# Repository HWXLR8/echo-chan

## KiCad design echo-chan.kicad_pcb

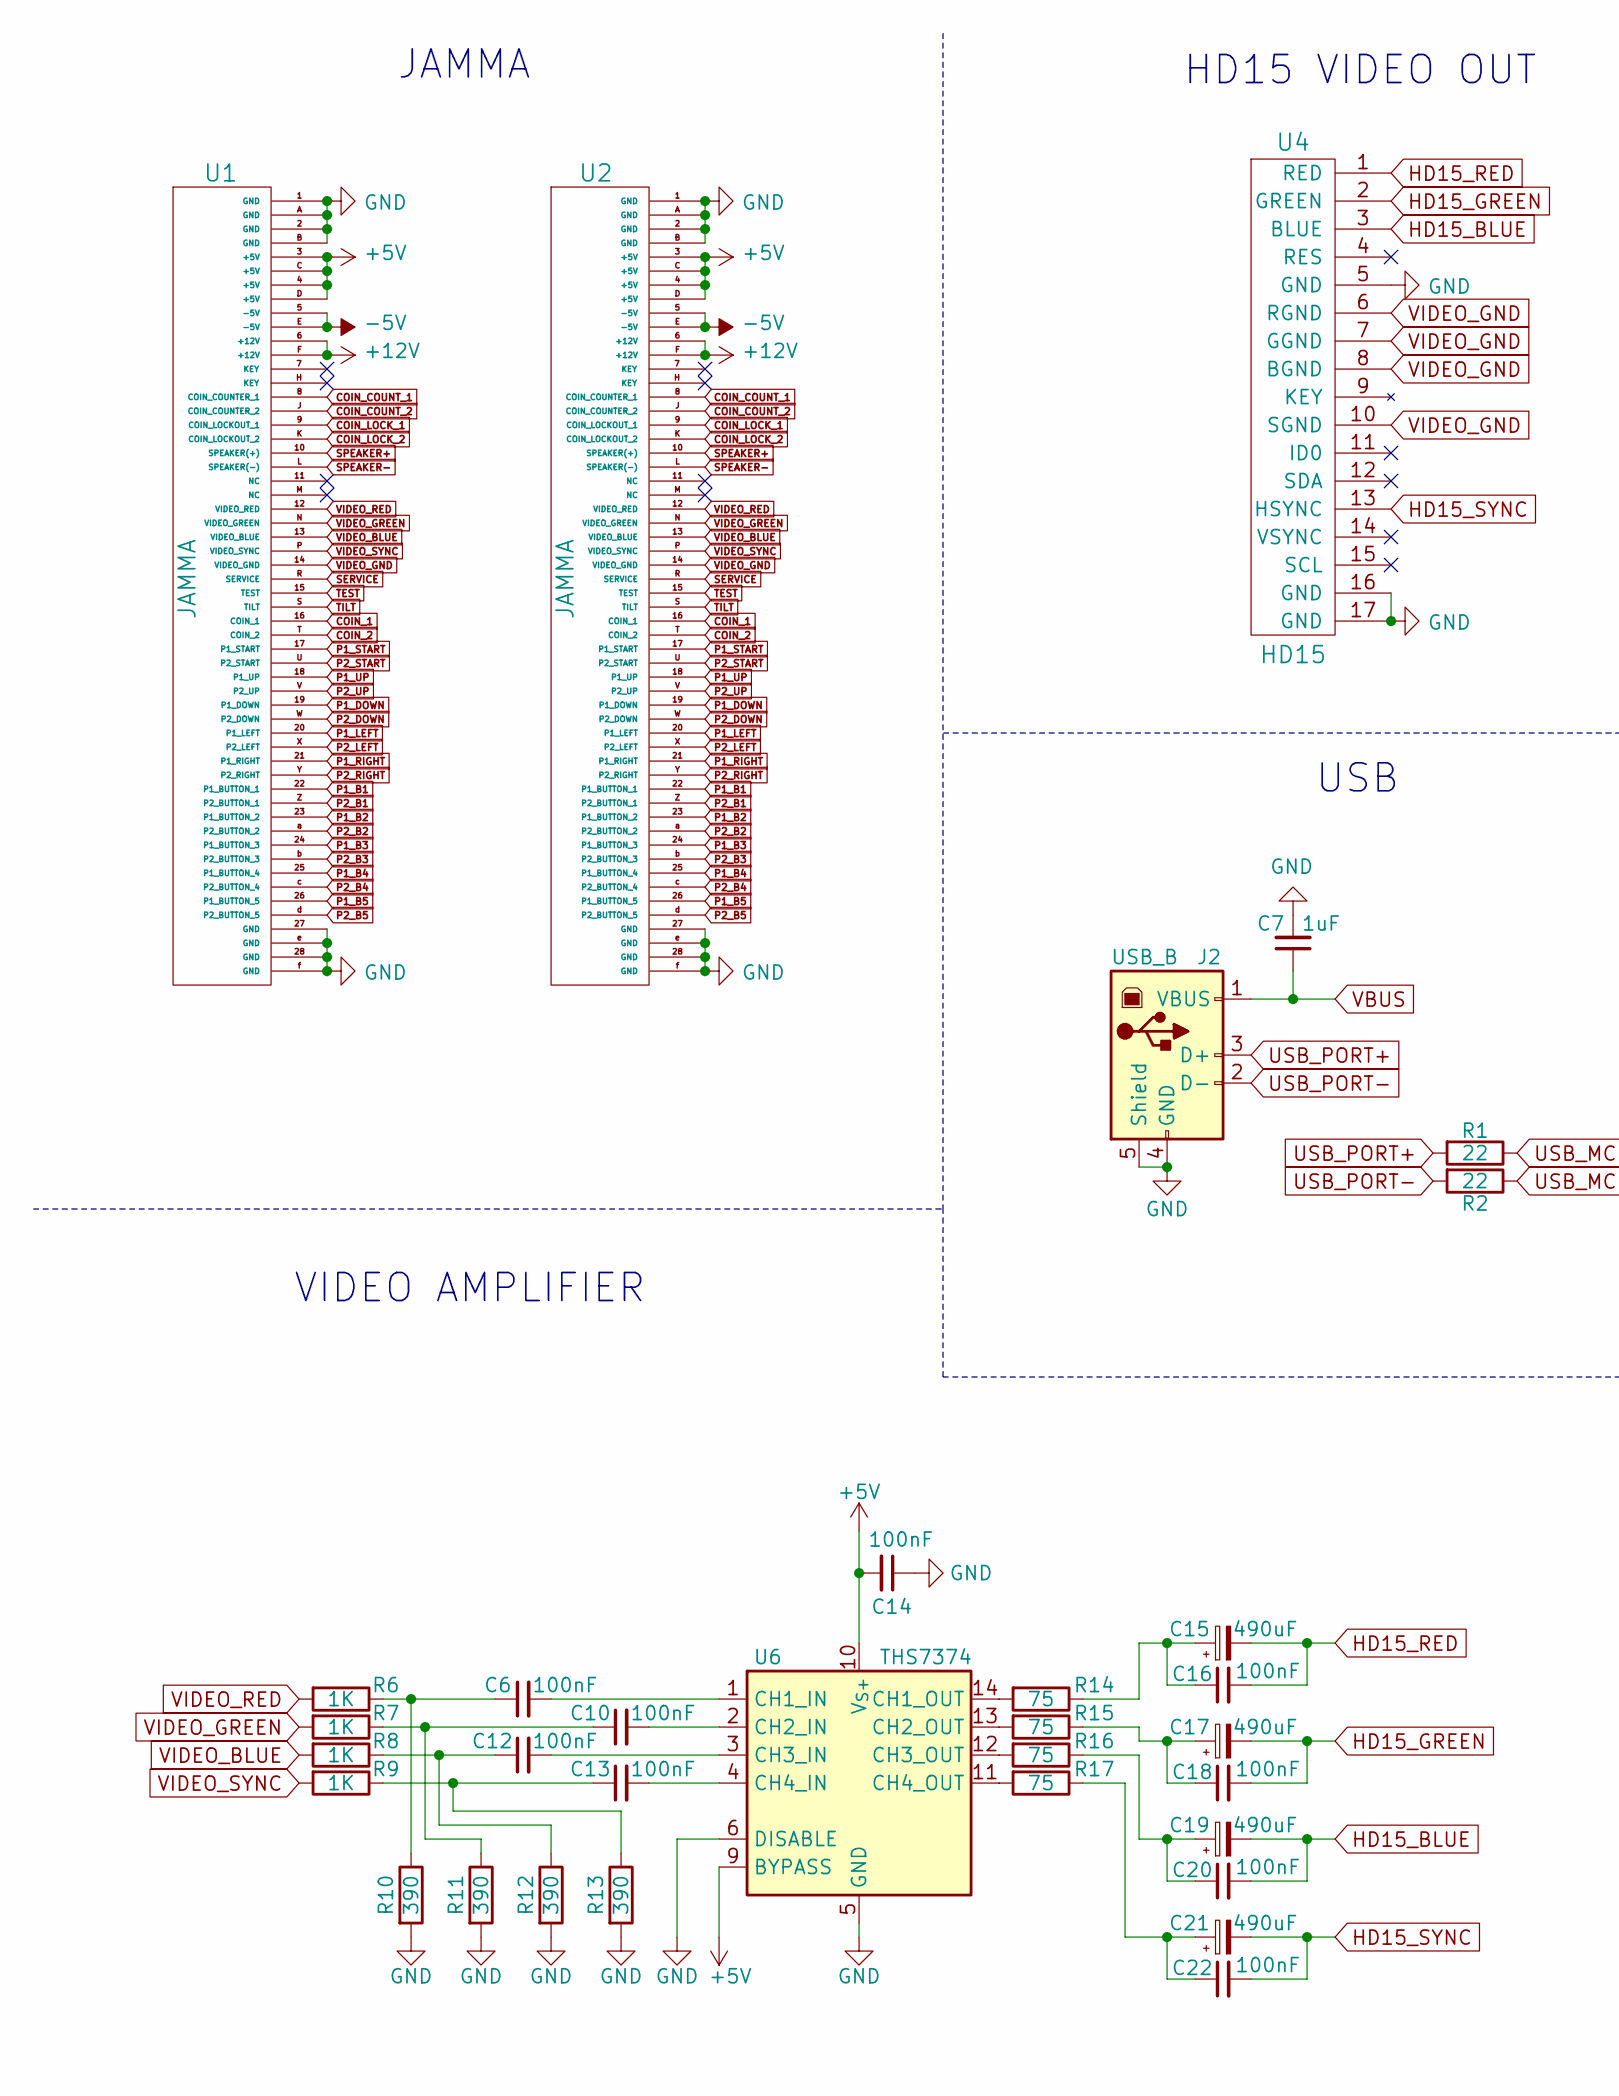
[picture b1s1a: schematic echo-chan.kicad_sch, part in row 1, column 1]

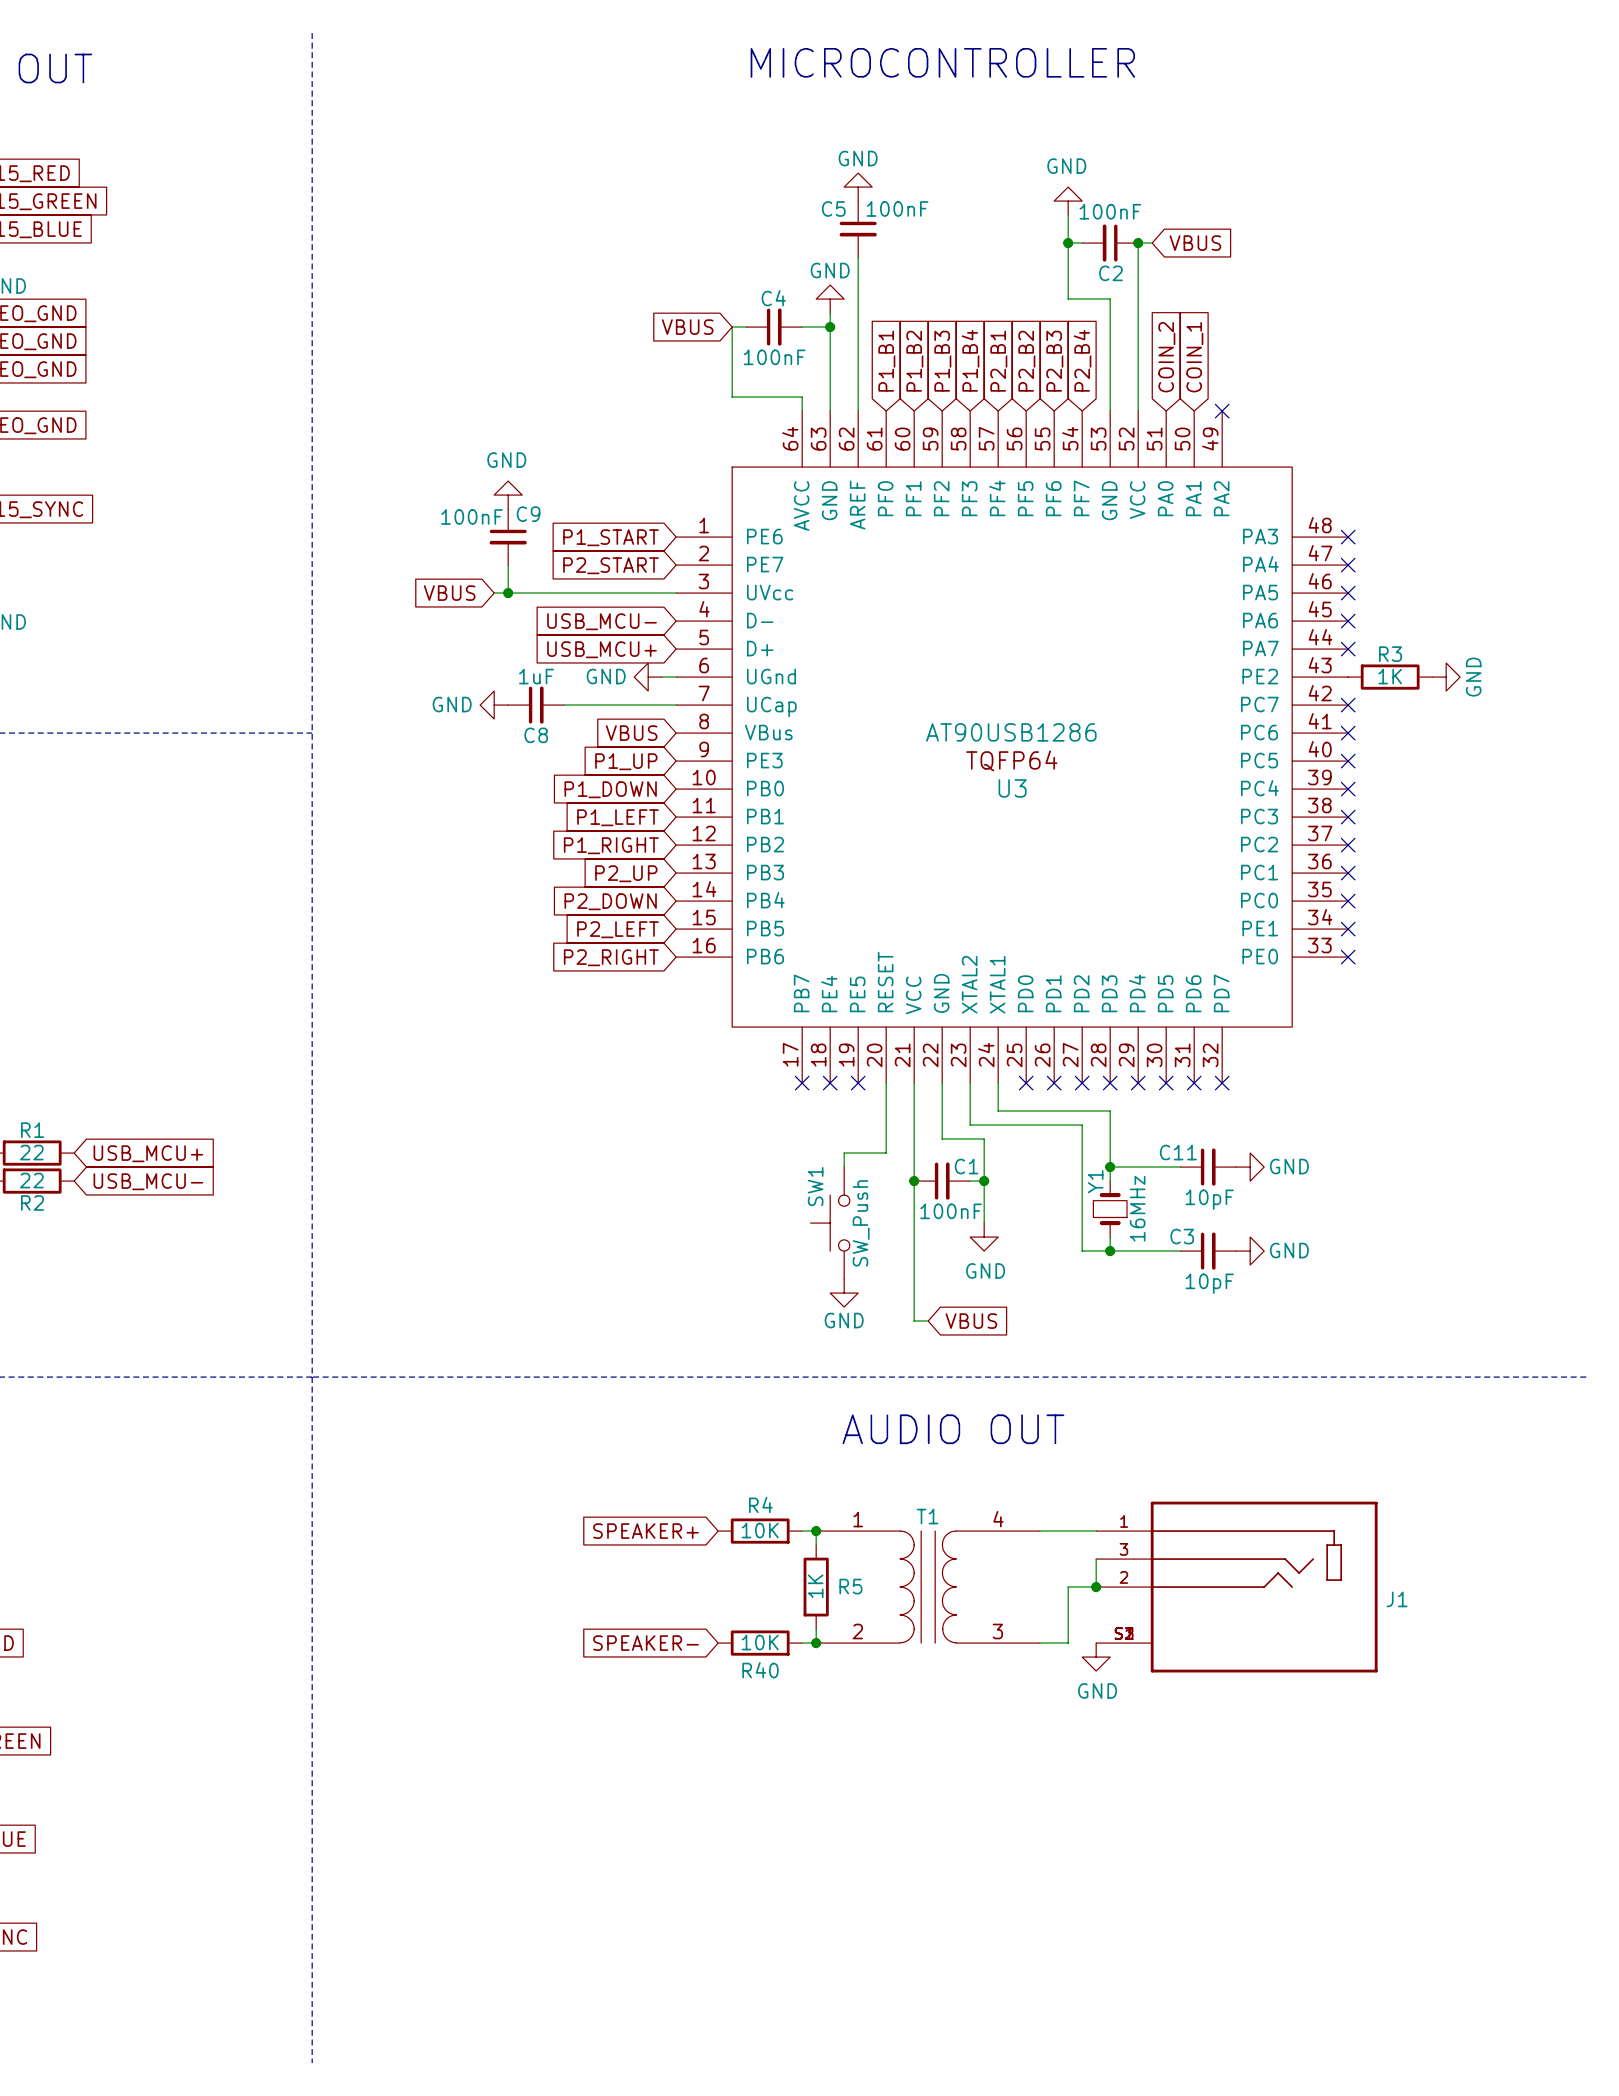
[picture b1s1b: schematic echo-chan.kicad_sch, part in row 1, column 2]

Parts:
C1, C2, C4, C5, C6, C9, C10, C12, C13, C14, C16, C18, C20, C22: 100nF; C_0805_2012Metric
C3, C11: 10pF; C_0805_2012Metric
C7, C8: 1uF; C_0805_2012Metric
C15, C17, C19, C21: 490uF; CP_Radial_D8.0mm_P3.50mm
J1: SJ1-3533NS; CUI_SJ1-3533NS
J2: USB_B; USB_B_OST_USB-B1HSxx_Horizontal
R1, R2: 22; R_0805_2012Metric
R3, R5, R6, R7, R8, R9: 1K; R_0805_2012Metric
R4, R40: 10K; R_0805_2012Metric
R10, R11, R12, R13: 390; R_0805_2012Metric
R14, R15, R16, R17: 75; R_0805_2012Metric
SW1: SW_Push; SW_PUSH_6mm
T1: Transformer_1P_1S; 560G
U1, U2: JAMMA
U3: AT90USB1286; TQFP-64_14x14mm_P0.8mm
U4: HD15; DSUB-15-HD_Female_Horizontal_P2.29x2.54mm_EdgePinOffset9.40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
U6: THS7374; TSSOP-14_4.4x5mm_P0.65mm
Y1: 16MHz; Crystal_HC49-4H_Vertical

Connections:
+5V: C14.2, U1.3 (+5V), U1.4 (+5V), U1.C (+5V), U1.D (+5V), U2.3 (+5V), U2.4 (+5V), U2.C (+5V), U2.D (+5V), U6.9 (BYPASS), U6.10 (V_{S+})
+12V: U1.6 (+12V), U1.F (+12V), U2.6 (+12V), U2.F (+12V)
-5V: U1.5 (-5V), U1.E (-5V), U2.5 (-5V), U2.E (-5V)
COIN_1: U1.16 (COIN_1), U2.16 (COIN_1), U3.50 (PA1)
COIN_2: U1.T (COIN_2), U2.T (COIN_2), U3.51 (PA0)
COIN_COUNT_1: U1.8 (COIN_COUNTER_1), U2.8 (COIN_COUNTER_1)
COIN_COUNT_2: U1.J (COIN_COUNTER_2), U2.J (COIN_COUNTER_2)
COIN_LOCK_1: U1.9 (COIN_LOCKOUT_1), U2.9 (COIN_LOCKOUT_1)
COIN_LOCK_2: U1.K (COIN_LOCKOUT_2), U2.K (COIN_LOCKOUT_2)
GND: C1.2, C2.2, C3.2, C4.2, C5.1, C7.2, C8.1, C9.1, C11.2, C14.1, J1.S1 (SHIELD), J1.S2 (SHIELD), J1.S3 (SHIELD), J2.4 (GND), J2.5 (Shield), R3.1, R10.2, R11.2, R12.2, R13.2, SW1.1, U1.1 (GND), U1.2 (GND), U1.27 (GND), U1.28 (GND), U1.A (GND), U1.B (GND), U1.e (GND), U1.f (GND), U2.1 (GND), U2.2 (GND), U2.27 (GND), U2.28 (GND), U2.A (GND), U2.B (GND), U2.e (GND), U2.f (GND), U3.6 (UGnd), U3.22 (GND), U3.53 (GND), U3.63 (GND), U4.5 (GND), U4.16 (GND), U4.17 (GND), U6.5 (GND), U6.6 (DISABLE)
HD15_BLUE: C19.2, C20.2, U4.3 (BLUE)
HD15_GREEN: C17.2, C18.2, U4.2 (GREEN)
HD15_RED: C15.2, C16.2, U4.1 (RED)
HD15_SYNC: C21.2, C22.2, U4.13 (HSYNC)
unnamed: C6.1, R6.1, R10.1
unnamed: C10.1, R7.1, R11.1
unnamed: C12.1, R8.1, R12.1
unnamed: C13.1, R9.1, R13.1
unnamed: C15.1, C16.1, R14.1
unnamed: C17.1, C18.1, R15.1
unnamed: C19.1, C20.1, R16.1
unnamed: C21.1, C22.1, R17.1
unnamed: R4.2, R5.1, T1.1 (AA)
unnamed: R5.2, R40.2, T1.2 (AB)
unnamed: J1.2, J1.3, T1.3 (SA)
unnamed: J1.1, T1.4 (SB)
unnamed: C5.2, U3.62 (AREF)
unnamed: R3.2, U3.43 (PE2)
unnamed: SW1.2, U3.20 (RESET)
unnamed: C8.2, U3.7 (UCap)
unnamed: C11.1, U3.24 (XTAL1), Y1.2
unnamed: C3.1, U3.23 (XTAL2), Y1.1
unnamed: C6.2, U6.1 (CH1_IN)
unnamed: R14.2, U6.14 (CH1_OUT)
unnamed: C10.2, U6.2 (CH2_IN)
unnamed: R15.2, U6.13 (CH2_OUT)
unnamed: C12.2, U6.3 (CH3_IN)
unnamed: R16.2, U6.12 (CH3_OUT)
unnamed: C13.2, U6.4 (CH4_IN)
unnamed: R17.2, U6.11 (CH4_OUT)
P1_B1: U1.22 (P1_BUTTON_1), U2.22 (P1_BUTTON_1), U3.61 (PF0)
P1_B2: U1.23 (P1_BUTTON_2), U2.23 (P1_BUTTON_2), U3.60 (PF1)
P1_B3: U1.24 (P1_BUTTON_3), U2.24 (P1_BUTTON_3), U3.59 (PF2)
P1_B4: U1.25 (P1_BUTTON_4), U2.25 (P1_BUTTON_4), U3.58 (PF3)
P1_B5: U1.26 (P1_BUTTON_5), U2.26 (P1_BUTTON_5)
P1_DOWN: U1.19 (P1_DOWN), U2.19 (P1_DOWN), U3.10 (PB0)
P1_LEFT: U1.20 (P1_LEFT), U2.20 (P1_LEFT), U3.11 (PB1)
P1_RIGHT: U1.21 (P1_RIGHT), U2.21 (P1_RIGHT), U3.12 (PB2)
P1_START: U1.17 (P1_START), U2.17 (P1_START), U3.1 (PE6)
P1_UP: U1.18 (P1_UP), U2.18 (P1_UP), U3.9 (PE3)
P2_B1: U1.Z (P2_BUTTON_1), U2.Z (P2_BUTTON_1), U3.57 (PF4)
P2_B2: U1.a (P2_BUTTON_2), U2.a (P2_BUTTON_2), U3.56 (PF5)
P2_B3: U1.b (P2_BUTTON_3), U2.b (P2_BUTTON_3), U3.55 (PF6)
P2_B4: U1.c (P2_BUTTON_4), U2.c (P2_BUTTON_4), U3.54 (PF7)
P2_B5: U1.d (P2_BUTTON_5), U2.d (P2_BUTTON_5)
P2_DOWN: U1.W (P2_DOWN), U2.W (P2_DOWN), U3.14 (PB4)
P2_LEFT: U1.X (P2_LEFT), U2.X (P2_LEFT), U3.15 (PB5)
P2_RIGHT: U1.Y (P2_RIGHT), U2.Y (P2_RIGHT), U3.16 (PB6)
P2_START: U1.U (P2_START), U2.U (P2_START), U3.2 (PE7)
P2_UP: U1.V (P2_UP), U2.V (P2_UP), U3.13 (PB3)
SERVICE: U1.R (SERVICE), U2.R (SERVICE)
SPEAKER+: R4.1, U1.10 (SPEAKER(+)), U2.10 (SPEAKER(+))
SPEAKER-: R40.1, U1.L (SPEAKER(-)), U2.L (SPEAKER(-))
TEST: U1.15 (TEST), U2.15 (TEST)
TILT: U1.S (TILT), U2.S (TILT)
USB_MCU+: R1.1, U3.5 (D+)
USB_MCU-: R2.1, U3.4 (D-)
USB_PORT+: J2.3 (D+), R1.2
USB_PORT-: J2.2 (D-), R2.2
VBUS: C1.1, C2.1, C4.1, C7.1, C9.2, J2.1 (VBUS), U3.3 (UVcc), U3.8 (VBus), U3.21 (VCC), U3.52 (VCC), U3.64 (AVCC)
VIDEO_BLUE: R8.2, U1.13 (VIDEO_BLUE), U2.13 (VIDEO_BLUE)
VIDEO_GND: U1.14 (VIDEO_GND), U2.14 (VIDEO_GND), U4.6 (RGND), U4.7 (GGND), U4.8 (BGND), U4.10 (SGND)
VIDEO_GREEN: R7.2, U1.N (VIDEO_GREEN), U2.N (VIDEO_GREEN)
VIDEO_RED: R6.2, U1.12 (VIDEO_RED), U2.12 (VIDEO_RED)
VIDEO_SYNC: R9.2, U1.P (VIDEO_SYNC), U2.P (VIDEO_SYNC)

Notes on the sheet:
VIDEO AMPLIFIER
USB
MICROCONTROLLER
AUDIO OUT
HD15 VIDEO OUT
JAMMA

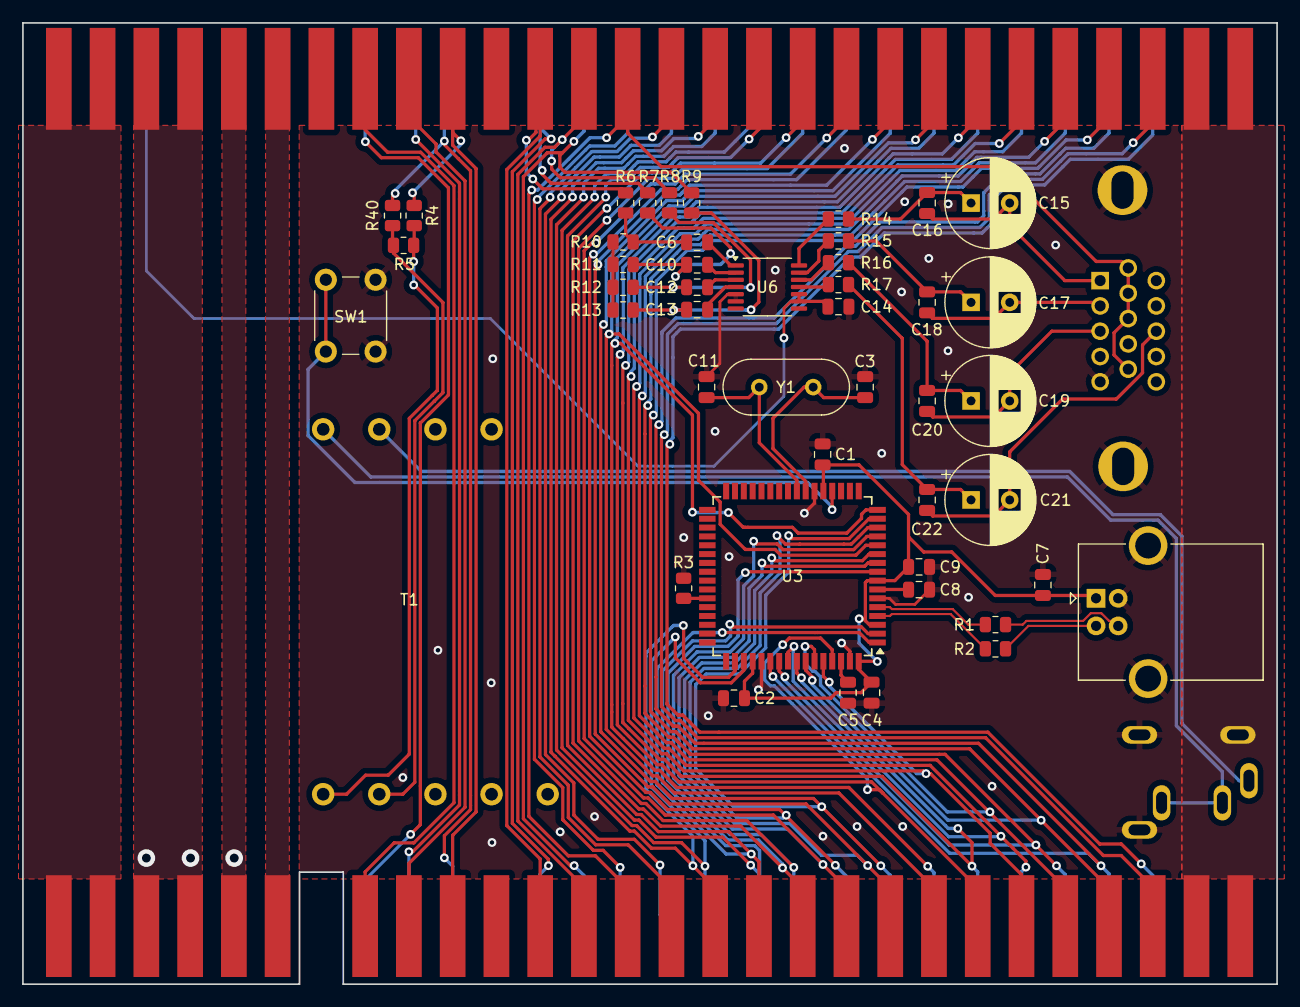
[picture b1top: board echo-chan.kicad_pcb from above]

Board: 2 copper layers, 113.5 x 87.0 mm, 50 parts (0 on the bottom side), 75 nets.

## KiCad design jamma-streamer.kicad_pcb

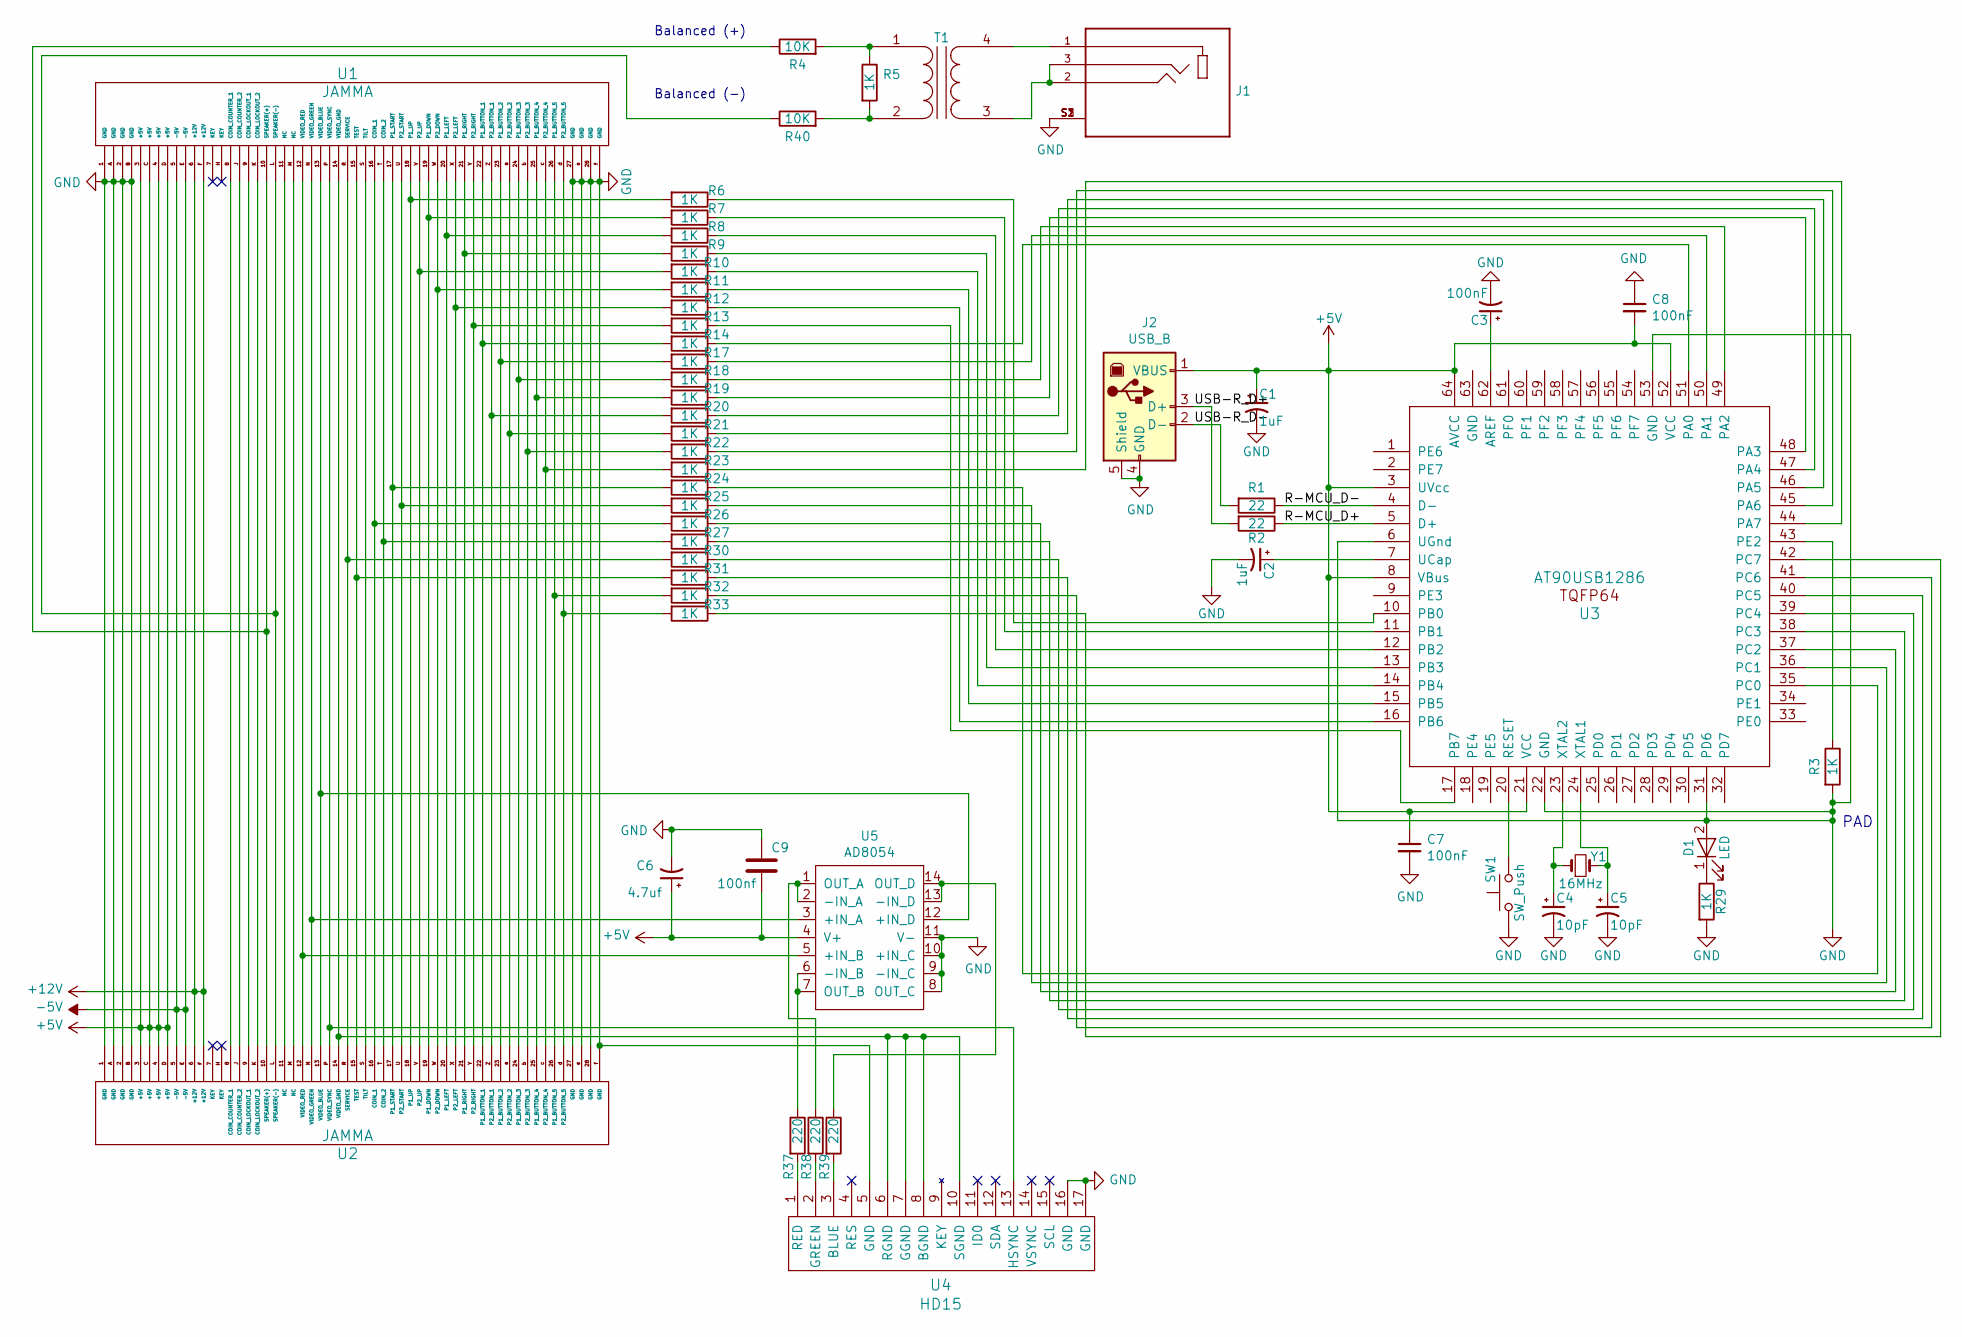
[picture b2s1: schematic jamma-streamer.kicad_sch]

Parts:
C1, C2: 1uF; C_0603_1608Metric
C3, C7, C8: 100nF; C_0603_1608Metric
C4, C5: 10pF; C_0603_1608Metric
C6: 4.7uf; C_1206_3216Metric_Pad1.42x1.75mm_HandSolder
C9: 100nf; C_0603_1608Metric
D1: LED; LED_0603_1608Metric
J1: SJ1-3533NS; CUI_SJ1-3533NS
J2: USB_B; USB_B_OST_USB-B1HSxx_Horizontal
R1, R2: 22; R_0805_2012Metric
R3, R5, R6, R7, R8, R9, R10, R11, R12, R13, R14, R17, R18, R19, R20, R21, R22, R23, R24, R25, R26, R27, R29, R30, R31, R32, R33: 1K; R_0805_2012Metric
R4, R40: 10K; R_0805_2012Metric
R37, R38, R39: 220; R_0805_2012Metric
SW1: SW_Push; BUTTON
T1: Transformer_1P_1S; 560G
U1, U2: JAMMA
U3: AT90USB1286; TQFP-64_14x14mm_P0.8mm
U4: HD15; DSUB-15-HD_Female_Horizontal_P2.29x2.54mm_EdgePinOffset9.40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
U5: AD8054; AD8054ARZ-REEL7
Y1: 16MHz; Crystal_SMD_SeikoEpson_FA238-4Pin_3.2x2.5mm

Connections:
+5V: C1.1, C6.1, C7.1, C8.2, C9.2, J2.1 (VBUS), U1.3 (+5V), U1.4 (+5V), U1.C (+5V), U1.D (+5V), U2.3 (+5V), U2.4 (+5V), U2.C (+5V), U2.D (+5V), U3.3 (UVcc), U3.8 (VBus), U3.21 (VCC), U3.52 (VCC), U3.64 (AVCC), U5.4 (V+)
+12V: U1.6 (+12V), U1.F (+12V), U2.6 (+12V), U2.F (+12V)
-5V: U1.5 (-5V), U1.E (-5V), U2.5 (-5V), U2.E (-5V)
/R-MCU_D+: R2.1, U3.5 (D+)
/R-MCU_D-: R1.1, U3.4 (D-)
/USB-R_D+: J2.3 (D+), R2.2
/USB-R_D-: J2.2 (D-), R1.2
unnamed: C2.1, U3.7 (UCap)
unnamed: C3.1, U3.62 (AREF)
unnamed: C4.1, U3.23 (XTAL2), Y1.1
unnamed: C5.1, U3.24 (XTAL1), Y1.2
unnamed: D1.1 (K), R29.1
unnamed: J1.1, T1.4 (SB)
unnamed: J1.2, J1.3, T1.3 (SA)
unnamed: R3.1, U3.43 (PE2)
unnamed: R4.1, U1.10 (SPEAKER(+)), U2.10 (SPEAKER(+))
unnamed: R4.2, R5.1, T1.1 (AA)
unnamed: R6.1, U3.10 (PB0)
unnamed: R6.2, U1.18 (P1_UP), U2.18 (P1_UP)
unnamed: R7.1, U3.11 (PB1)
unnamed: R7.2, U1.19 (P1_DOWN), U2.19 (P1_DOWN)
unnamed: R8.1, U3.12 (PB2)
unnamed: R8.2, U1.20 (P1_LEFT), U2.20 (P1_LEFT)
unnamed: R9.1, U3.13 (PB3)
unnamed: R9.2, U1.21 (P1_RIGHT), U2.21 (P1_RIGHT)
unnamed: R10.1, U3.14 (PB4)
unnamed: R10.2, U1.V (P2_UP), U2.V (P2_UP)
unnamed: R11.1, U3.15 (PB5)
unnamed: R11.2, U1.W (P2_DOWN), U2.W (P2_DOWN)
unnamed: R12.1, U3.16 (PB6)
unnamed: R12.2, U1.X (P2_LEFT), U2.X (P2_LEFT)
unnamed: R13.1, U3.17 (PB7)
unnamed: R13.2, U1.Y (P2_RIGHT), U2.Y (P2_RIGHT)
unnamed: R14.1, U3.51 (PA0)
unnamed: R14.2, U1.22 (P1_BUTTON_1), U2.22 (P1_BUTTON_1)
unnamed: R17.1, U3.50 (PA1)
unnamed: R17.2, U1.23 (P1_BUTTON_2), U2.23 (P1_BUTTON_2)
unnamed: R18.1, U3.49 (PA2)
unnamed: R18.2, U1.24 (P1_BUTTON_3), U2.24 (P1_BUTTON_3)
unnamed: R19.1, U3.48 (PA3)
unnamed: R19.2, U1.25 (P1_BUTTON_4), U2.25 (P1_BUTTON_4)
unnamed: R20.1, U3.47 (PA4)
unnamed: R20.2, U1.Z (P2_BUTTON_1), U2.Z (P2_BUTTON_1)
unnamed: R21.1, U3.46 (PA5)
unnamed: R21.2, U1.a (P2_BUTTON_2), U2.a (P2_BUTTON_2)
unnamed: R22.1, U3.45 (PA6)
unnamed: R22.2, U1.b (P2_BUTTON_3), U2.b (P2_BUTTON_3)
unnamed: R23.1, U3.44 (PA7)
unnamed: R23.2, U1.c (P2_BUTTON_4), U2.c (P2_BUTTON_4)
unnamed: R24.1, U3.35 (PC0)
unnamed: R24.2, U1.17 (P1_START), U2.17 (P1_START)
unnamed: R25.1, U3.36 (PC1)
unnamed: R25.2, U1.U (P2_START), U2.U (P2_START)
unnamed: R26.1, U3.37 (PC2)
unnamed: R26.2, U1.16 (COIN_1), U2.16 (COIN_1)
unnamed: R27.1, U3.38 (PC3)
unnamed: R27.2, U1.T (COIN_2), U2.T (COIN_2)
unnamed: R30.1, U3.39 (PC4)
unnamed: R30.2, U1.R (SERVICE), U2.R (SERVICE)
unnamed: R31.1, U3.40 (PC5)
unnamed: R31.2, U1.15 (TEST), U2.15 (TEST)
unnamed: R32.1, U3.41 (PC6)
unnamed: R32.2, U1.26 (P1_BUTTON_5), U2.26 (P1_BUTTON_5)
unnamed: R33.1, U3.42 (PC7)
unnamed: R33.2, U1.d (P2_BUTTON_5), U2.d (P2_BUTTON_5)
unnamed: R37.1, U5.6 (-IN_B), U5.7 (OUT_B)
unnamed: R37.2, U4.1 (RED)
unnamed: R38.1, U5.1 (OUT_A), U5.2 (-IN_A)
unnamed: R38.2, U4.2 (GREEN)
unnamed: R39.1, U5.13 (-IN_D), U5.14 (OUT_D)
unnamed: R39.2, U4.3 (BLUE)
unnamed: R40.1, U1.L (SPEAKER(-)), U2.L (SPEAKER(-))
unnamed: R5.2, R40.2, T1.2 (AB)
unnamed: SW1.2, U3.20 (RESET)
unnamed: U1.8 (COIN_COUNTER_1), U2.8 (COIN_COUNTER_1)
unnamed: U1.9 (COIN_LOCKOUT_1), U2.9 (COIN_LOCKOUT_1)
unnamed: U1.11 (NC), U2.11 (NC)
unnamed: U1.12 (VIDEO_RED), U2.12 (VIDEO_RED), U5.5 (+IN_B)
unnamed: U1.13 (VIDEO_BLUE), U2.13 (VIDEO_BLUE), U5.12 (+IN_D)
unnamed: U1.14 (VIDEO_GND), U2.14 (VIDEO_GND), U4.6 (RGND), U4.7 (GGND), U4.8 (BGND), U4.10 (SGND)
unnamed: U1.J (COIN_COUNTER_2), U2.J (COIN_COUNTER_2)
unnamed: U1.K (COIN_LOCKOUT_2), U2.K (COIN_LOCKOUT_2)
unnamed: U1.M (NC), U2.M (NC)
unnamed: U1.N (VIDEO_GREEN), U2.N (VIDEO_GREEN), U5.3 (+IN_A)
unnamed: U1.P (VIDEO_SYNC), U2.P (VIDEO_SYNC), U4.13 (HSYNC)
unnamed: U1.S (TILT), U2.S (TILT)

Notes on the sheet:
Balanced (+)
Balanced (-)
PAD

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
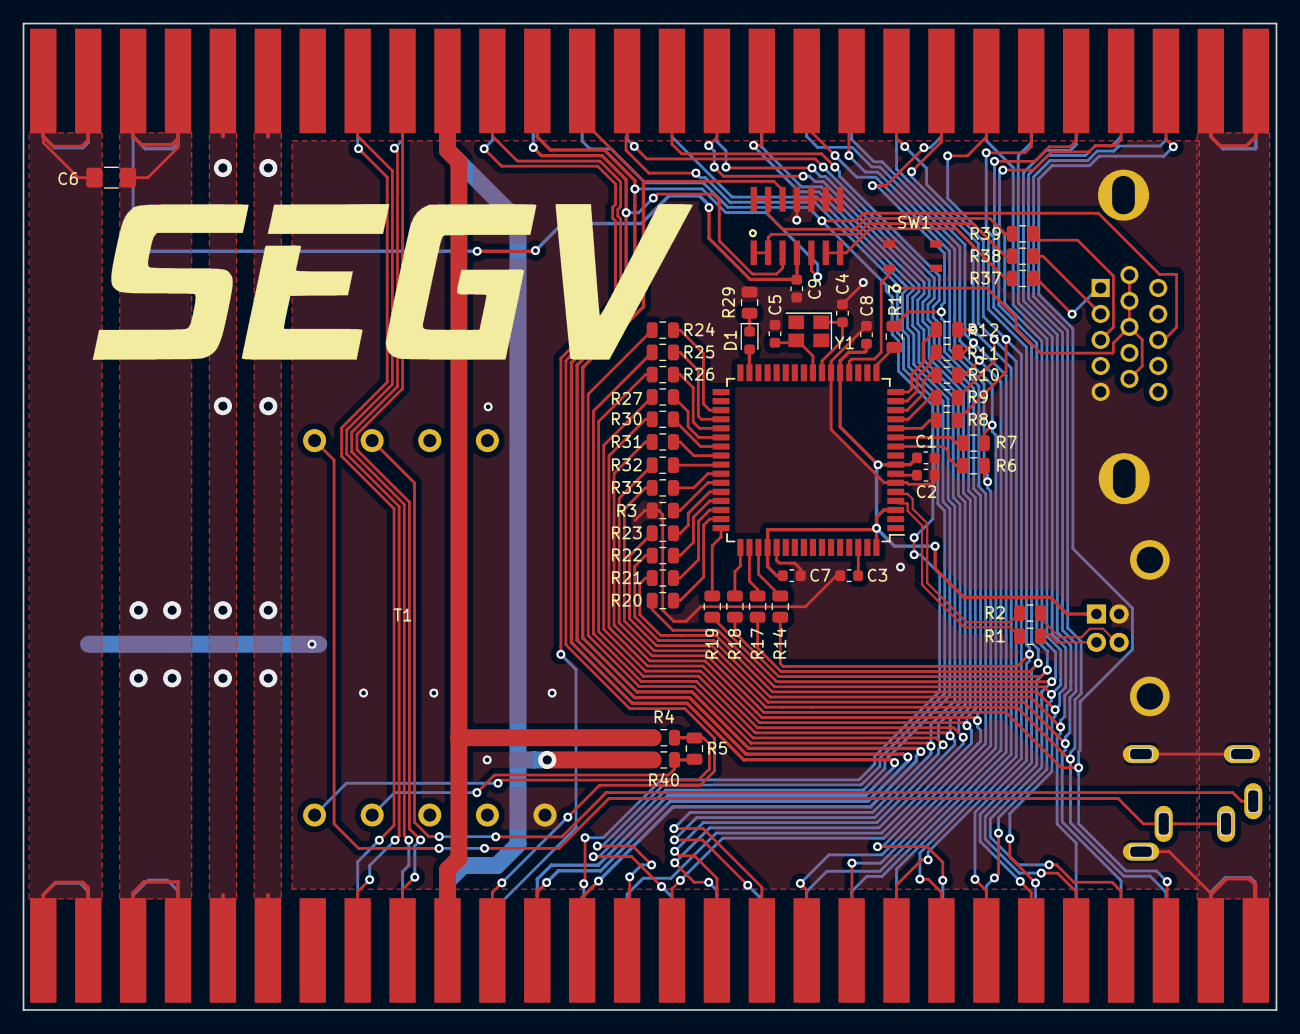
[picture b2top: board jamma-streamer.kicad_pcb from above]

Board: 2 copper layers, 110.5 x 87.0 mm, 54 parts (0 on the bottom side), 88 nets.

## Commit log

2024-05-04 init
2024-05-04 jamma-streamer -> echo-chan
2024-05-04 Schematic cleanup
    - separate +5V and GND lines for readability
    - remove useless resistors on MCU input lines
    - remove LED
    - Add NC sympbols to unused MCU pins
2024-05-05 [SCHEMATIC] Major schematic overhaul
    - Replace rats nest of wires with labels
    - Separate schematic into sections
    - Replace AD8054 with THS7374
2024-05-05 [SCHEMATIC] assign footprints to symbols
2024-05-05 [SCHEMATIC] Change +5V to VBUS for MCU
2024-05-05 [SCHEMATIC] Fix typos in schematic block labels
2024-05-05 [SCHEMATIC] Fix inverted U2 JAMMA edge
2024-05-05 [SCHEMATIC] MCU refactor
    - Remove test/service connections
    - Move all button inputs to 2 sides to simplify routing
2024-05-05 [SCHEMATIC] Minor cosmetic changes
2024-05-05 [PCB] Tentative layout complete
2024-05-05 [SCHEMATIC] Fix incorrect tag on HD15 green line
2024-05-09 checkpoint
2024-05-12 route done
2024-05-12 [PCB] Routing done
2024-05-12 [PCB] Move PCB files into their own directory
2024-05-12 [FW] Add firmware files
2024-05-12 [VIEWER] Add viewer files
2024-05-12 [PCB] Add silkscreen
2024-05-12 Add LICENSE

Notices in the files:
parts and their libraries:
Copyright 2016 Accelerated Designs. All rights reserved.
